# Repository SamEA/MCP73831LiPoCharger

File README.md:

MCP73831LiPoCharger
===================

A USB charger for Lithium and LiPo battery  MCP73831

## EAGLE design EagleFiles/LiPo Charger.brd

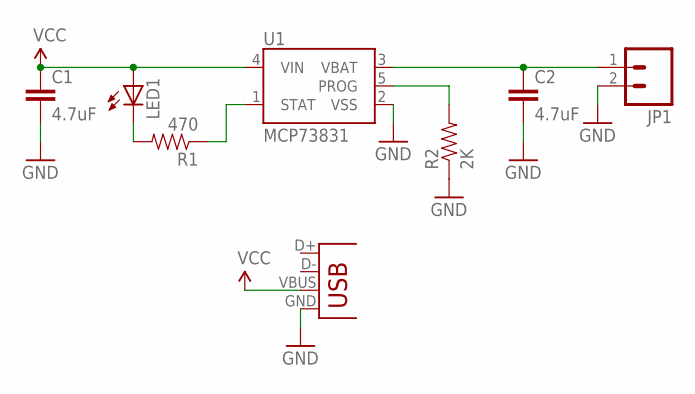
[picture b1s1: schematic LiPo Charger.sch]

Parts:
C1, C2: 4.7uF; 1206
JP1: M02POLAR; MOLEX-1X2
LED1: LEDCHIP-LED0603; CHIP-LED0603
R1: 470; 0805
R2: 2K; 0805
U1: MCP73831; SOT23-5
X1: USB; USB-A-MALE-SMT

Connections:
GND: C1.2, C2.2, JP1.2, R2.1, U1.2 (VSS), X1.GND
unnamed: LED1.C, R1.2
unnamed: R1.1, U1.1 (STAT)
unnamed: R2.2, U1.5 (PROG)
VBAT: C2.1, JP1.1, U1.3 (VBAT)
VCC: C1.1, LED1.A, U1.4 (VIN), X1.VBUS

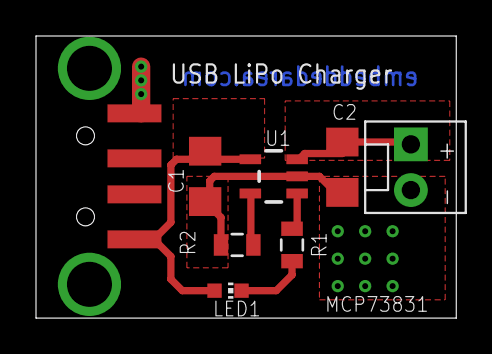
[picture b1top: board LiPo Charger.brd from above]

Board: 2 copper layers, 23.3 x 15.7 mm, 8 parts (0 on the bottom side), 6 nets.

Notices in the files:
parts and their libraries:
SparkFun-PowerIC: Licensing: CC v3.0 Share-Alike You are welcome to use this library for commercial purposes.
